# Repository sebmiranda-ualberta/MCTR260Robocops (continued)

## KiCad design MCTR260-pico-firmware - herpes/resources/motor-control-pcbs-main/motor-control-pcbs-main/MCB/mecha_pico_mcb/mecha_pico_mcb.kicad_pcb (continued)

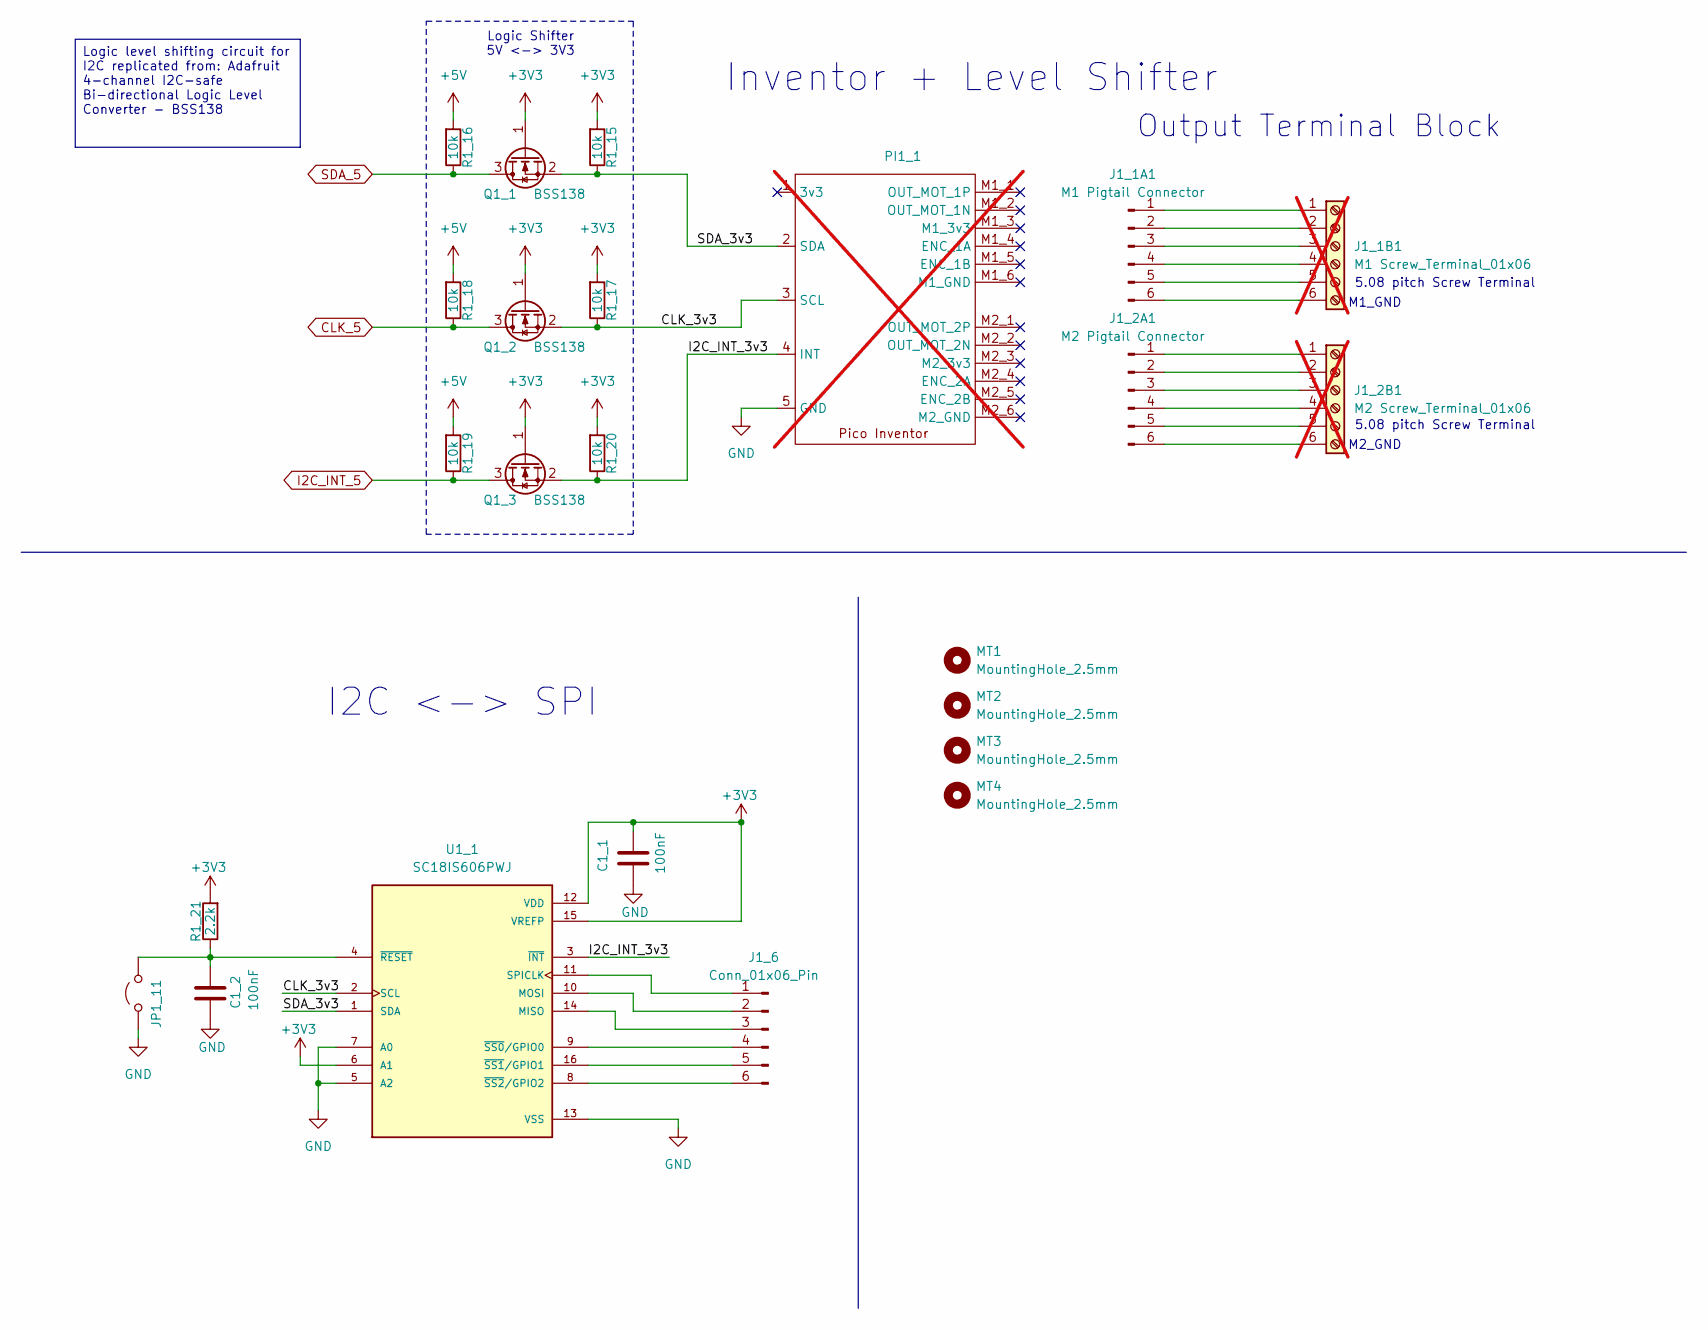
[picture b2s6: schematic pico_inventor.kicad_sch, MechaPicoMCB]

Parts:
C1_1, C1_2: 100nF; C_0603_1608Metric_Pad1.08x0.95mm_HandSolder; MPN C0603C104K5RACTU
J1_1A1: M1 Pigtail Connector; PinHeader_1x06_P1.27mm_Vertical
J1_1B1: M1 Screw_Terminal_01x06; CONN_OSTTC062162_OST; MPN OSTTC062162; not fitted
J1_2A1: M2 Pigtail Connector; PinHeader_1x06_P1.27mm_Vertical
J1_2B1: M2 Screw_Terminal_01x06; CONN_OSTTC062162_OST; MPN OSTTC062162; not fitted
J1_6: Conn_01x06_Pin; PinSocket_1x06_P2.54mm_Vertical; MPN PPTC061LFBN-RC
JP1_11: 2pin_1mil_Jmp; PinHeader_1x02_P2.54mm_Vertical; PartNote MaleHeader_2x1_1mil_&_header_con
MT1, MT2, MT3, MT4: MountingHole_2.5mm
PI1_1: PicoInventor; MPN PIM633; not fitted
Q1_1, Q1_2, Q1_3: BSS138; SOT-23; MPN BSS138
R1_15, R1_16, R1_17, R1_18, R1_19, R1_20: 10k; R_0603_1608Metric_Pad0.98x0.95mm_HandSolder; MPN RC0603FR-7W10KL
R1_21: 2.2k; R_0603_1608Metric_Pad0.98x0.95mm_HandSolder; MPN AC0603FR-7W2K2L
U1_1: SC18IS606PWJ; SOP65P640X110-16N; PARTREV 1.0

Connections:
+3V3: C1_1.1, Q1_1.1 (G), Q1_2.1 (G), Q1_3.1 (G), R1_15.2, R1_17.2, R1_20.2, R1_21.2, U1_1.6 (A1), U1_1.12 (VDD), U1_1.15 (VREFP); also elsewhere on the board
+5V: R1_16.2, R1_18.2, R1_19.2; also elsewhere on the board
/PicoInventor/CLK_3v3: PI1_1.3 (SCL), Q1_2.2 (S), R1_17.1, U1_1.2 (SCL)
/PicoInventor/I2C_INT_3v3: PI1_1.4 (INT), Q1_3.2 (S), R1_20.1, U1_1.3 (~INT)
/PicoInventor/SDA_3v3: PI1_1.2 (SDA), Q1_1.2 (S), R1_15.1, U1_1.1 (SDA)
CLK_5: Q1_2.3 (D), R1_18.1; also elsewhere on the board
GND: C1_1.2, C1_2.2, JP1_11.1 (A), PI1_1.5 (GND), U1_1.5 (A2), U1_1.7 (A0), U1_1.13 (VSS); also elsewhere on the board
I2C_INT_5: Q1_3.3 (D), R1_19.1; also elsewhere on the board
unnamed: J1_1A1.1, J1_1B1.1
unnamed: J1_1A1.2, J1_1B1.2
unnamed: J1_1A1.3, J1_1B1.3
unnamed: J1_1A1.4, J1_1B1.4
unnamed: J1_1A1.5, J1_1B1.5
unnamed: J1_1A1.6, J1_1B1.6
unnamed: J1_2A1.1, J1_2B1.1
unnamed: J1_2A1.2, J1_2B1.2
unnamed: J1_2A1.3, J1_2B1.3
unnamed: J1_2A1.4, J1_2B1.4
unnamed: J1_2A1.5, J1_2B1.5
unnamed: J1_2A1.6, J1_2B1.6
unnamed: J1_6.1, U1_1.11 (SPICLK)
unnamed: J1_6.2, U1_1.10 (MOSI)
unnamed: J1_6.3, U1_1.14 (MISO)
unnamed: J1_6.4, U1_1.9 (~SS0/GPIO0)
unnamed: J1_6.5, U1_1.16 (~SS1/GPIO1)
unnamed: J1_6.6, U1_1.8 (~SS2/GPIO2)
unnamed: C1_2.1, JP1_11.2 (B), R1_21.1, U1_1.4 (~RESET)
SDA_5: Q1_1.3 (D), R1_16.1; also elsewhere on the board

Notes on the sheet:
5.08 pitch Screw Terminal
M2_GND
M1_GND
Inventor + Level Shifter
Output Terminal Block
Logic Shifter 5V <-> 3V3
I2C <-> SPI
Logic level shifting circuit for I2C replicated from: Adafruit 4-channel I2C-safe Bi-directional Logic Level Converter - BSS138

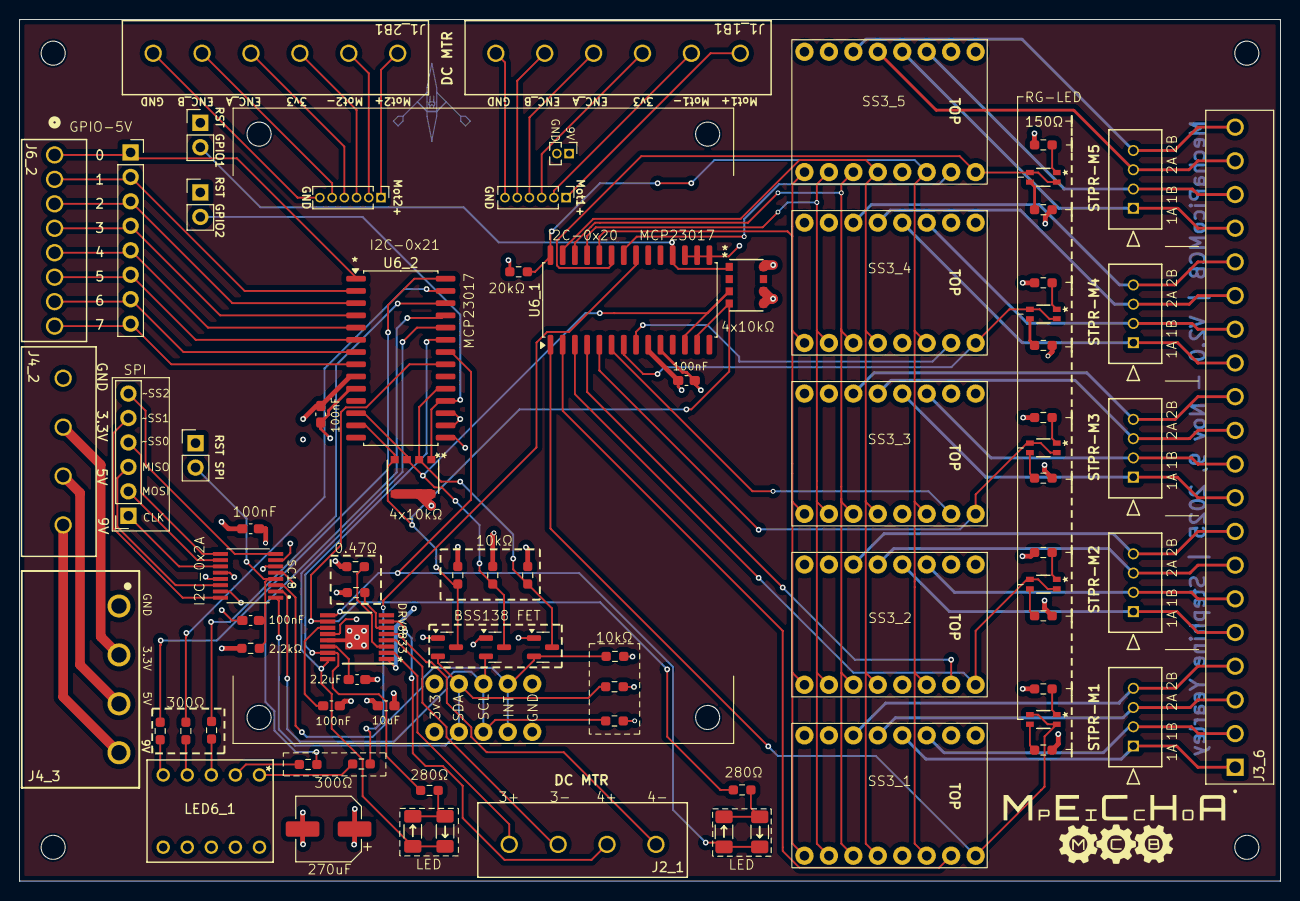
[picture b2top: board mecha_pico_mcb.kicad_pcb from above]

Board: 4 copper layers, 131.0 x 89.5 mm, 84 parts (0 on the bottom side), 108 nets.

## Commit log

2026-03-27 current code v11
2026-03-27 upload working code as well
